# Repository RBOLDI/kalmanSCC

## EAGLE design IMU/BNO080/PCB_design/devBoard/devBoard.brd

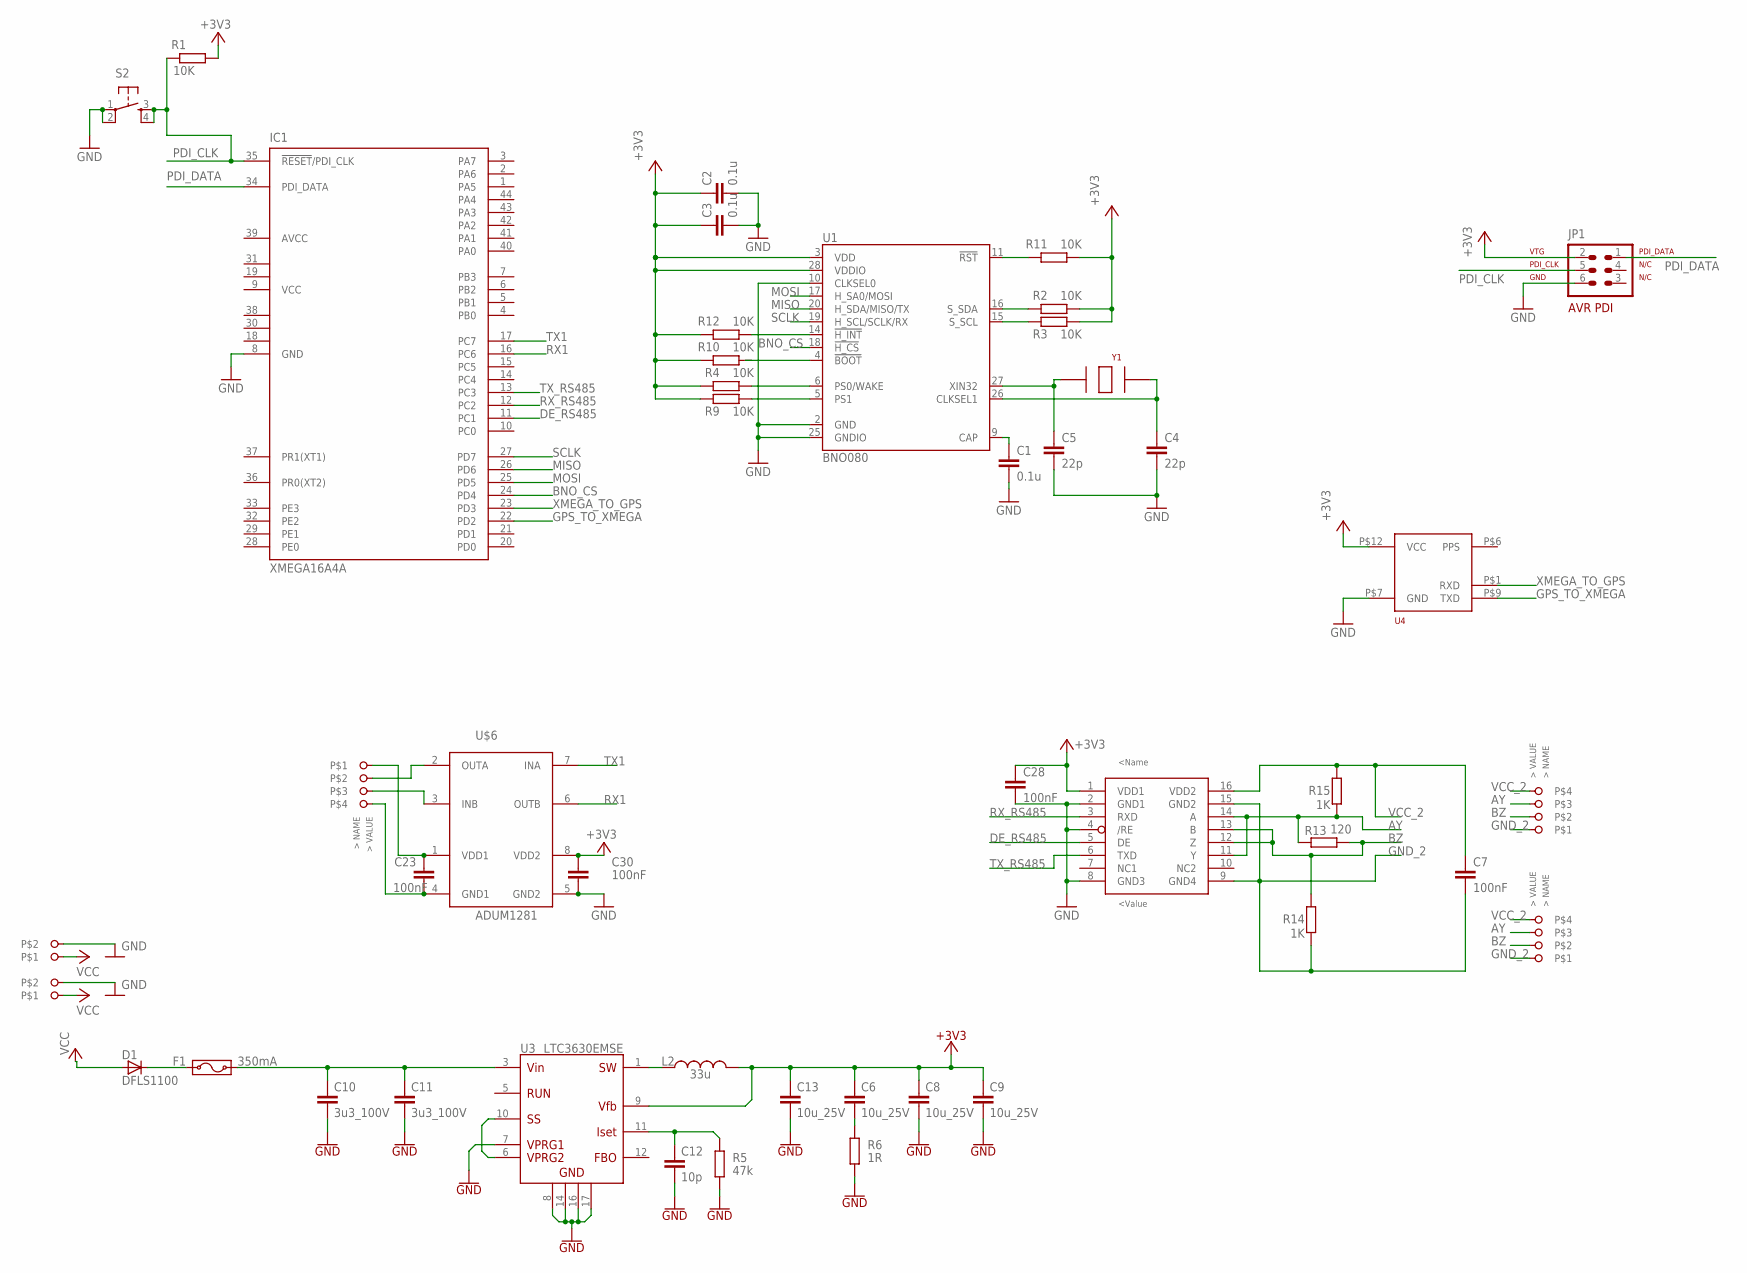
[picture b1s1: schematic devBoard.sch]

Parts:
ADM1: ADM2484E; ADM2487
C1, C2, C3: 0.1u; C0805
C4, C5: 22p; C0805
C6, C8, C9, C13: 10u_25V; 1206
C7, C23, C28, C30: 100nF; C0805
C10, C11: 3u3_100V; 1206
C12: 10p; 0805
D1: DFLS1100; POWERDI_123
F1: 350mA; 1812L
IC1: XMEGA16A4A; TQFP44
JP1: AVR-ISP-6ML; ML6
L2: 33u; DR73/74
POWER1, POWER2: CON_3.81MM2_SIDE
R1, R2, R3, R4, R9, R10, R11, R12: 10K; R0805
R5: 47k; 0805
R6: 1R; 0805
R13: 120; R0805
R14, R15: 1K; R0805
S2: TAC_SWITCHPTH; TACTILE-PTH
SERIEEL, SERIEEL1, SERIEEL2: CON_3,5MM4_SIDE
U1: BNO080; LGA-28
U3: LTC3630EMSE; MSE16(12)
U4: NAVSPARK_MININAVSPARK_MINI; NAVSPARK_MINI
U$6: ADUM1281; SOIC8
Y1: ABS07

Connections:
+3V3: ADM1.1 (VDD1), C2.1, C3.1, C6.1, C8.1, C9.1, C13.1, C28.1, C30.2, JP1.2, L2.2, R1.1, R2.1, R3.1, R4.2, R9.2, R10.2, R11.1, R12.2, U1.3 (VDD), U1.28 (VDDIO), U3.9 (VFB), U4.P$12 (VCC), U$6.8 (VDD2)
AVCC: IC1.39 (AVCC)
AY: ADM1.11 (Y), ADM1.14 (A), R13.2, R15.1, SERIEEL1.P3, SERIEEL2.P3
BNO080_BOOT: R10.1, U1.4 (!BOOT)
BNO_CS: IC1.24 (PD4), U1.18 (!H_CS)
BZ: ADM1.12 (Z), ADM1.13 (B), R13.1, R14.2, SERIEEL1.P2, SERIEEL2.P2
DE_RS485: ADM1.5 (DE), IC1.11 (PC1)
GND: ADM1.2 (GND1), ADM1.4 (/RE), ADM1.8 (GND3), C1.2, C2.2, C3.2, C4.2, C5.2, C8.2, C9.2, C10.2, C11.2, C12.2, C13.2, C28.2, C30.1, IC1.8 (GND), JP1.6, POWER1.P$2, POWER2.P$2, R5.2, R6.2, S2.1, S2.2, U1.2 (GND), U1.10 (CLKSEL0), U1.25 (GNDIO), U3.7 (VPRG1), U3.8 (GND1), U3.14 (GND2), U3.16 (GND3), U3.17 (GND4), U4.P$7 (GND), U$6.5 (GND2)
GND1: IC1.18 (GND1)
GND2: IC1.30 (GND2)
GND3: IC1.38 (GND3)
GND4: C23.1, SERIEEL.P4, U$6.4 (GND1)
GND_2: ADM1.9 (GND4), ADM1.15 (GND2), C7.2, R14.1, SERIEEL1.P1, SERIEEL2.P1
GPS_TO_XMEGA: IC1.22 (PD2), U4.P$9 (TXD)
INB: SERIEEL.P3, U$6.3 (INB)
MISO: IC1.26 (PD6), U1.20 (H_SDA/MISO/TX)
MOSI: IC1.25 (PD5), U1.17 (H_SA0/MOSI)
unnamed: C1.1, U1.9 (CAP)
unnamed: C10.1, C11.1, F1.2, U3.3 (VIN)
unnamed: D1.C, F1.1
unnamed: C5.1, U1.27 (XIN32), Y1.P$2
unnamed: C4.1, U1.26 (CLKSEL1), Y1.P$1
unnamed: R2.2, U1.16 (S_SDA)
unnamed: R3.2, U1.15 (S_SCL)
unnamed: R4.1, U1.6 (PS0/WAKE)
unnamed: R9.1, U1.5 (PS1)
unnamed: R11.2, U1.11 (!RST)
unnamed: U3.6 (VPRG2), U3.10 (SS)
unnamed: R12.1, U1.14 (!H_INT)
unnamed: C12.1, R5.1, U3.11 (ISET)
unnamed: L2.1, U3.1 (SW)
unnamed: C6.2, R6.1
OUTA: SERIEEL.P2, U$6.2 (OUTA)
PDI_CLK: IC1.35 (!RESET!/PDI_CLK), JP1.5, R1.2, S2.3, S2.4
PDI_DATA: IC1.34 (PDI_DATA), JP1.1
RX1: IC1.16 (PC6), U$6.6 (OUTB)
RX_RS485: ADM1.3 (RXD), IC1.12 (PC2)
SCLK: IC1.27 (PD7), U1.19 (H_SCL/SCLK/RX)
TX1: IC1.17 (PC7), U$6.7 (INA)
TX_RS485: ADM1.6 (TXD), IC1.13 (PC3)
VCC: D1.A, POWER1.P$1, POWER2.P$1
VCC1: IC1.19 (VCC1)
VCC2: IC1.31 (VCC2)
VCC_2: ADM1.16 (VDD2), C7.1, IC1.9 (VCC), R15.2, SERIEEL1.P4, SERIEEL2.P4
VDD_1: C23.2, SERIEEL.P1, U$6.1 (VDD1)
XMEGA_TO_GPS: IC1.23 (PD3), U4.P$1 (RXD)

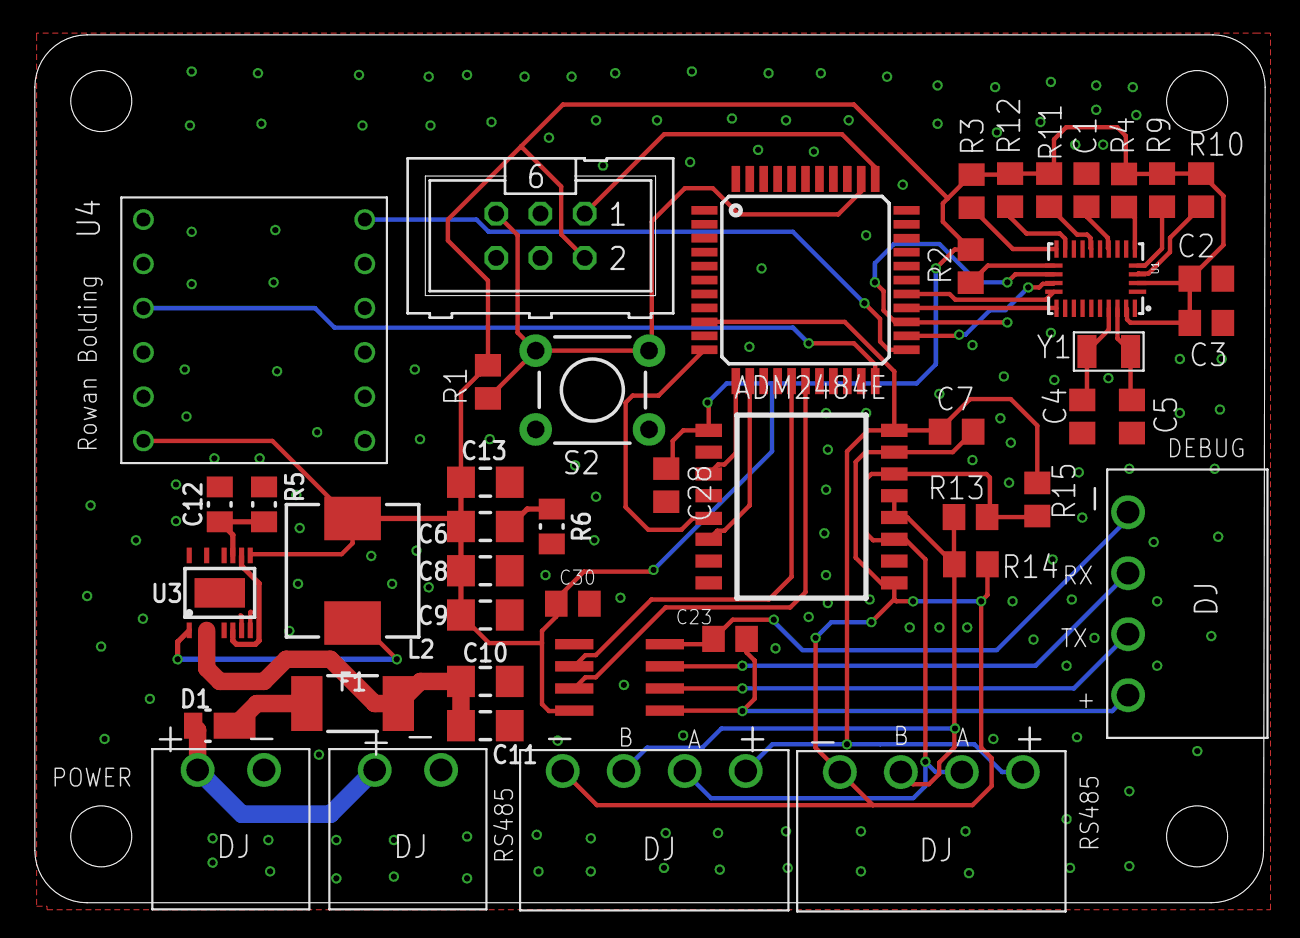
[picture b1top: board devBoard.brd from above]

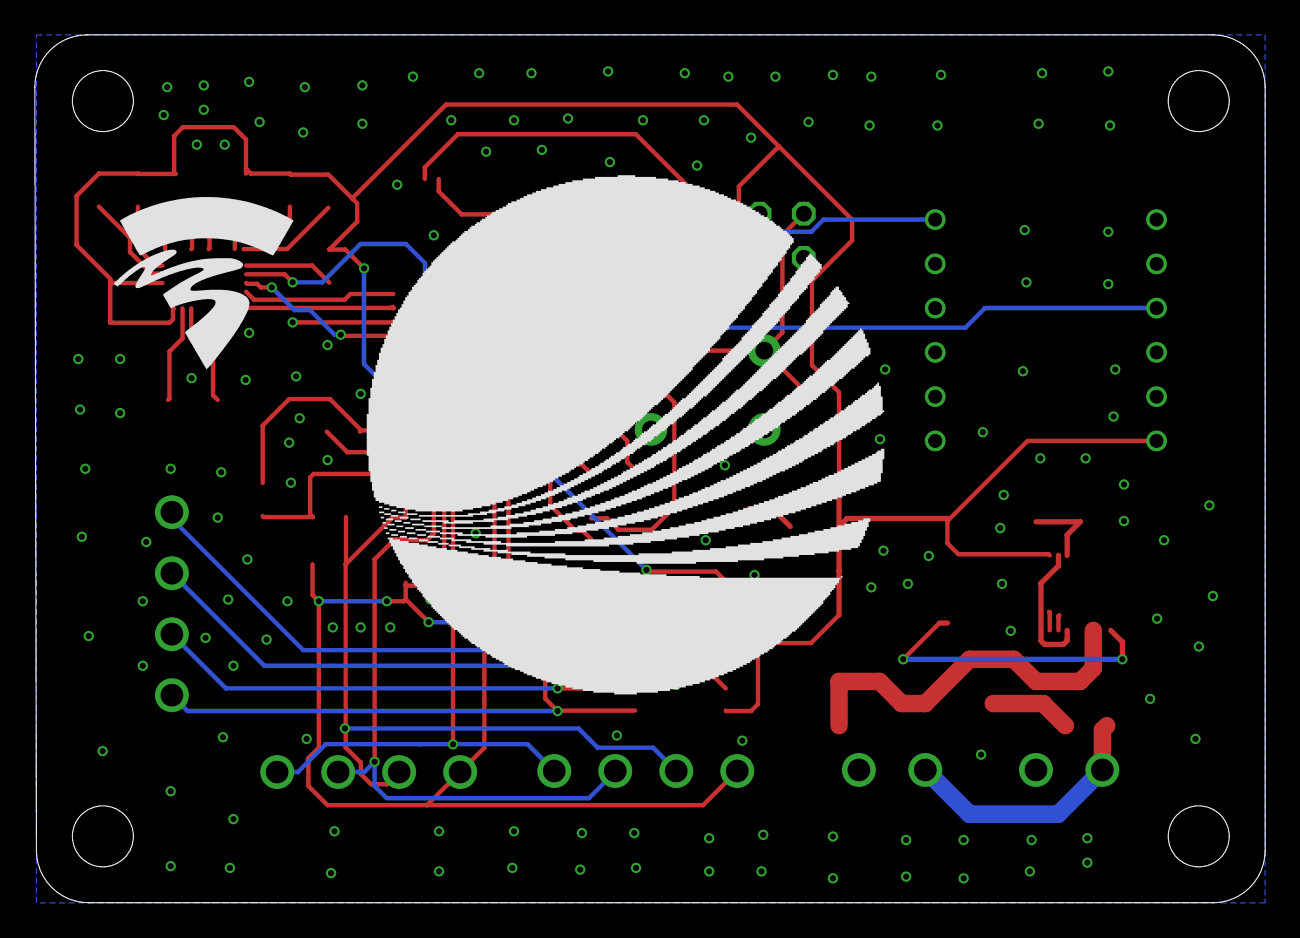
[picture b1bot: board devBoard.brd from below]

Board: 2 copper layers, 70.6 x 49.8 mm, 48 parts (2 on the bottom side), 40 nets.

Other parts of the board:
U$1: LOGO_KLEIN
U$2: HVA_LOGO

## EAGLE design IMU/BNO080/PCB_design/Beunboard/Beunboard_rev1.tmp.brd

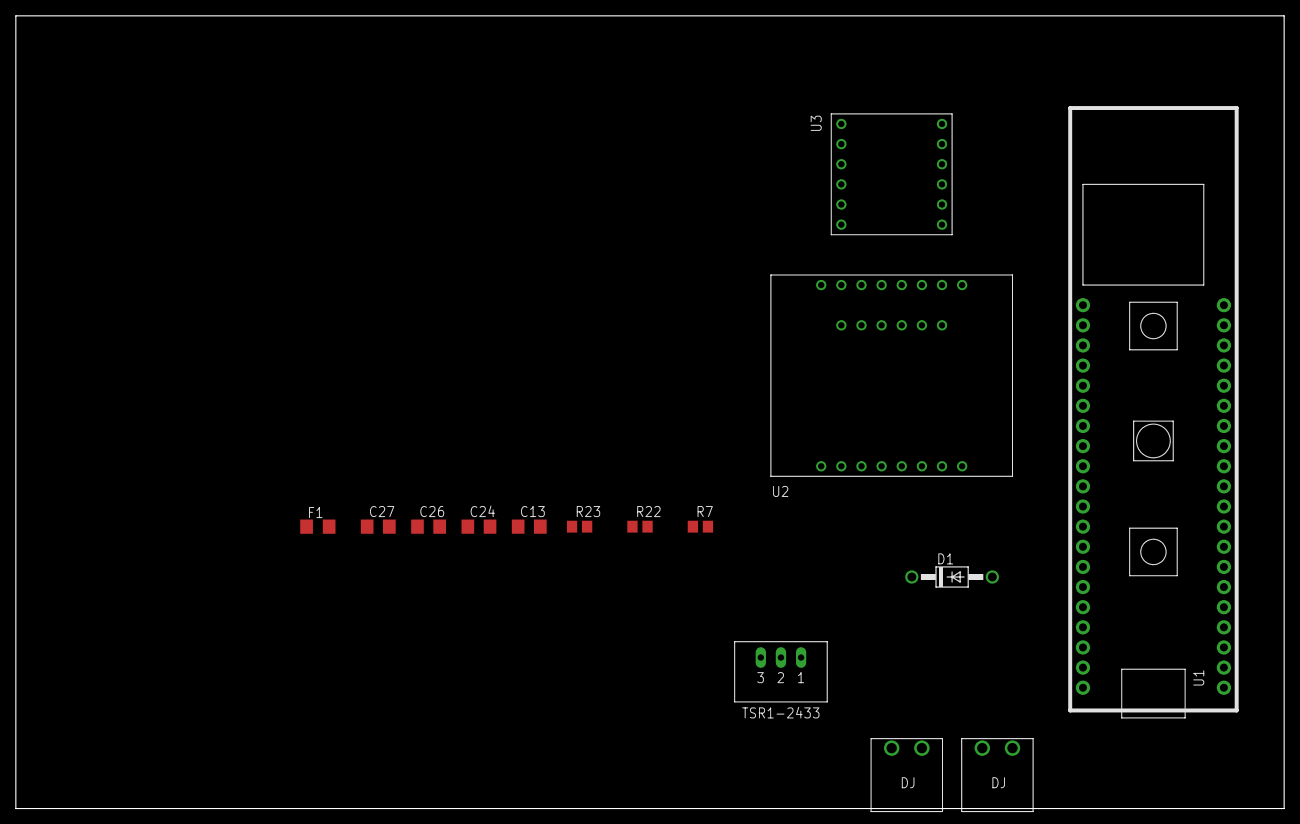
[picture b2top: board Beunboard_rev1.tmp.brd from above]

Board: 2 copper layers, 160.0 x 100.0 mm, 15 parts (0 on the bottom side), 14 nets, no tracks yet.

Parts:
C13, C27: 10uF; C1206
C24, C26: 22uF; C1206
D1: 1N4004; DO41-10
F1: 350mA; R1206
POWER1, POWER2: CON_3.81MM2_SIDE
R7: 0.2 Ohm; R0805
R22, R23: 1 Ohm; R0805
TSR1-2433: TSR1-2433
U1: XMEGABOARD-REV1.00-20150419DIP; XMEGABOARD-REV1.00-20150419
U2: SPARKFUN_BNO080SPARKFUN_BNO080; SPARKFUN_BNO080
U3: NAVSPARK_MININAVSPARK_MINI; NAVSPARK_MINI

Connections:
+3V3: C26.1, C27.1, TSR1-2433.VO, U1.P$11, U2.P$2, U2.P$8, U2.P$18, U3.P$12
+24V: C13.1, C24.1, R7.1, TSR1-2433.VI
CS: U1.P$15, U2.P$6
GND: C13.2, C27.2, D1.A, POWER1.P$2, POWER2.P$2, R22.2, R23.1, TSR1-2433.GND, U1.P$02, U1.P$20, U1.P$21, U1.P$30, U1.P$39, U2.P$1, U2.P$17, U3.P$7
GPS_TO_XMEGA: U1.P$17, U3.P$9
MISO: U1.P$14, U2.P$4
MOSI: U1.P$13, U2.P$5
unnamed: C26.2, R22.1
unnamed: C24.2, R23.2
unnamed: D1.C, F1.2, R7.2
SPI_CLK: U1.P$12, U2.P$3
VCC: F1.1, POWER1.P$1, POWER2.P$1
WAKE: U1.P$18, U2.P$7
XMEGA_TO_GPS: U1.P$16, U3.P$1

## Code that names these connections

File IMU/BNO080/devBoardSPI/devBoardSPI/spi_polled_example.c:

/* This file has been prepared for Doxygen automatic documentation generation.*/
/*! \file *********************************************************************
 *
 * \brief  XMEGA SPI polled driver example source.
 *
 *      This file contains an example application that demonstrates the polled
 *      SPI drivers.
 *
 * \par Application note:
 *      AVR1309: Using the XMEGA SPI
 *
 * \par Documentation
 *      For comprehensive code documentation, supported compilers, compiler
 *      settings and supported devices see readme.html
 *
 * \author
 *      Atmel Corporation: http://www.atmel.com \n
 *      Support email: avr@atmel.com
 *
 * $Revision: 5407 $
 * $Date: 2011-10-12 14:53:14 +0200 (on, 12 okt 2011) $  \n
 *
 * Copyright (c) 2009 Atmel Corporation. All rights reserved.
 *
 * Redistribution and use in source and binary forms, with or without
 * modification, are permitted provided that the following conditions are met:
 *
 * 1. Redistributions of source code must retain the above copyright notice,
 * this list of conditions and the following disclaimer.
 *
 * 2. Redistributions in binary form must reproduce the above copyright notice,
 * this list of conditions and the following disclaimer in the documentation
 * and/or other materials provided with the distribution.
 *
 * 3. The name of Atmel may not be used to endorse or promote products derived
 * from this software without specific prior written permission.

 * 4. This software may only be redistributed and used in connection with an
 * Atmel AVR product.

 * THIS SOFTWARE IS PROVIDED BY ATMEL "AS IS" AND ANY EXPRESS OR IMPLIED
 * WARRANTIES, INCLUDING, BUT NOT LIMITED TO, THE IMPLIED WARRANTIES OF
 * MERCHANTABILITY, FITNESS FOR A PARTICULAR PURPOSE AND NON-INFRINGEMENT ARE
 * EXPRESSLY AND SPECIFICALLY DISCLAIMED. IN NO EVENT SHALL ATMEL BE LIABLE FOR
 * ANY DIRECT, INDIRECT, INCIDENTAL, SPECIAL, EXEMPLARY, OR CONSEQUENTIAL
 * DAMAGES (INCLUDING, BUT NOT LIMITED TO, PROCUREMENT OF SUBSTITUTE GOODS OR
 * SERVICES; LOSS OF USE, DATA, OR PROFITS; OR BUSINESS INTERRUPTION) HOWEVER
 * CAUSED AND ON ANY THEORY OF LIABILITY, WHETHER IN CONTRACT, STRICT LIABILITY,
 * OR TORT (INCLUDING NEGLIGENCE OR OTHERWISE) ARISING IN ANY WAY OUT OF THE USE
 * OF THIS SOFTWARE, EVEN IF ADVISED OF THE POSSIBILITY OF SUCH DAMAGE.
 *****************************************************************************/

#include "avr_compiler.h"
#include "spi_driver.h"


/*! \brief The number of test data bytes. */
#define NUM_BYTES			4
#define ID_REQUEST_BYTES	2

/* Global variables */

/*! \brief SPI master module on PORT D. */
SPI_Master_t spiMasterD;

/*! \brief SPI Data packet */
SPI_DataPacket_t dataPacket;

/*! \brief Test data to send from master. */
uint8_t masterSendData[NUM_BYTES] = {0x11, 0x22, 0x33, 0x44};
	
/*! \BNO080 product ID Reqquest. */
uint8_t BNO080_IDrequest[ID_REQUEST_BYTES] = {0xF9, 0x00};

/*! \brief Data received from slave. */
uint8_t masterReceivedData[32];

/*! \brief Result of the test. */
bool success = true;



/*! \brief Test function.
 *
 *  This function tests the SPI master drivers in polled operation,
 *  with a master (on port D).
 *
 *  Hardware setup:
 *
 *    - Connect PD4  (SS)
 *    - Connect PD5  (MOSI)
 *    - Connect PD6  (MISO)
 *    - Connect PD7  (SCK)
 *
 *  The drivers are tested in two phases:
 *
 *  1: Data is transmitted on byte at a time from the master to the slave.
 *     The slave increments the received data and sends it back. The master reads
 *     the data from the slave and verifies that it equals the data sent + 1.
 *
 *  2: Data is transmitted 4 bytes at a time to the slave. As the master sends
 *     a byte to the slave, the preceding byte is sent back to the master.
 *     When all bytes have been sent, it is verified that the last 3 bytes
 *     received at the master, equal the first 3 bytes sent.
 *
 *  The variable, 'success', will be non-zero when the function reaches the
 *  infinite for-loop if the test was successful.
 */
int main(void)
{
	/* Init SS pin as output with wired AND and pull-up. */
	PORTD.DIRSET = PIN4_bm;
	PORTD.PIN4CTRL = PORT_OPC_WIREDANDPULL_gc;

	/* Set SS output to high. (No slave addressed). */
	PORTD.OUTSET = PIN4_bm;

	/* Instantiate pointer to ssPort. */
	PORT_t *ssPort = &PORTD;

	/* Initialize SPI master on port D. */
	SPI_MasterInit(&spiMasterD,
	               &SPID,
	               &PORTD,
	               false,
	               SPI_MODE_0_gc,
	               SPI_INTLVL_OFF_gc,
	               false,
	               SPI_PRESCALER_DIV4_gc);
	
	
	/* MASTER: Release SS to slave. */
	SPI_MasterSSHigh(ssPort, PIN4_bm);

	/* PHASE 1: Transceive data packet. */

	/* Create data packet (SS to slave by PD4). */
	SPI_MasterCreateDataPacket(&dataPacket,
	                           BNO080_IDrequest,
	                           masterReceivedData,
	                           NUM_BYTES,
	                           &PORTD,
	                           PIN4_bm);

	/* Transceive packet. */
	SPI_MasterTransceivePacket(&spiMasterD, &dataPacket);

	/* Check that correct data was received. Assume success at first. */
	if (masterReceivedData[0] == 0xF8) {
		PORTC.DIRSET = PIN0_bm;
		PORTC.OUTSET = PIN0_bm;
	}
	while(true) {
		nop();
	}
}

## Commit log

2020-01-08 Kalman cleaner verbetert, Kalmanset maker verbetert
2020-01-10 BNO080 datasheet en manual toegevoegd
2020-01-16 spi.c en spi.h opgesteld
2020-01-22 devboard schema's toegevoegd, info over kalibratie toegevoegd
2020-01-28 DevBoard rev 1 af: Bus, Debug, Navspark mini, BNO080
2020-02-05 AVR SPI exmpl, board designs
2020-03-20 ID Response, linAcc output correct
2020-03-20 de setup van de calibratie routine
2020-03-22 ongebruikte code weg, bron over sensorFusion toegevoegd
2020-03-25 Kalibratie routines gescheven
    Zoek naar verbetering om bij alle 3 de sensoren de status bit naar 3 te krijgen.
2020-09-02 RotationVector received
    continue to rotationMatrix
2020-09-02 Rotationmatrix formula implemented
2020-09-02 Inverse matrix calculation complete
2020-09-03 Acceleration rotation complete
    the acceleration is now rotated relative to the magnetic north!
2020-09-16 Able to receive GPS NMEA sentences

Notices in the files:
parts and their libraries:
SparkFun-Electromechanical: Licensing: CC v3.0 Share-Alike You are welcome to use this library for commercial purposes.
